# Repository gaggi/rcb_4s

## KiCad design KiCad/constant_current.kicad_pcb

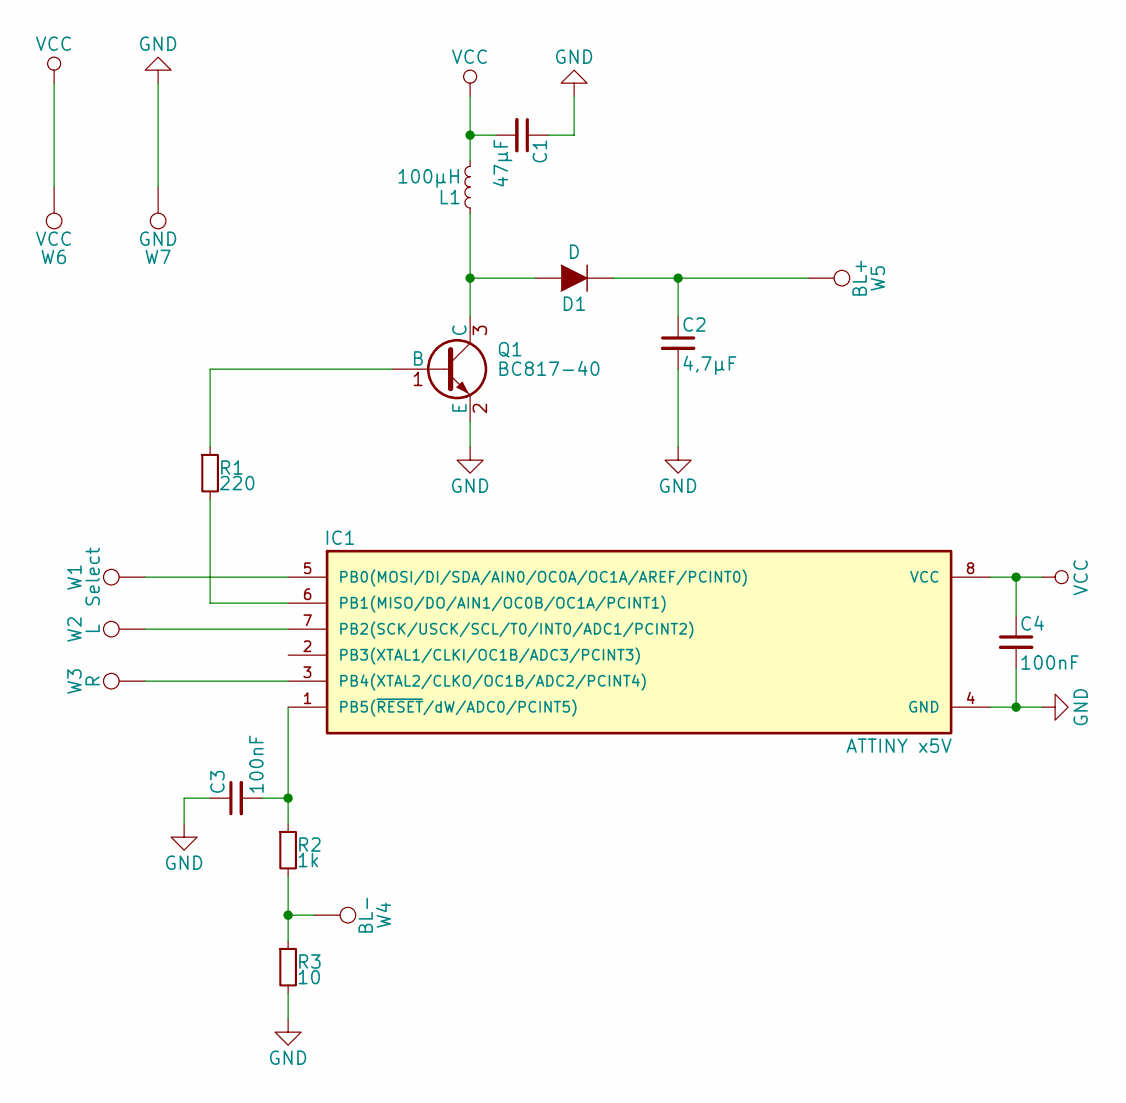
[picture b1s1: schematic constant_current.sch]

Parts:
C1: 47µF; C_1210
C2: 4,7µF; C_1210
C3, C4: 100nF; C_0805
D1: D; D_SOD-323_HandSoldering
IC1: ATTINY x5V; SOIC-8-N
L1: 100µH; 1212fps-inductor
Q1: BC817-40; SOT-23
R1: 220; R_0805
R2: 1k; R_0805
R3: 10; R_0805
W1: Select; 1Pin
W2: L; 1Pin
W3: R; 1Pin
W4: BL-; 1Pin
W5: BL+; 1Pin
W6: VCC; 1Pin
W7: GND; 1Pin

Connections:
GND: C1.1, C2.2, C3.1, C4.2, IC1.4 (GND), Q1.2 (E), R3.2, W7.1; also elsewhere on the board
unnamed: C2.1, D1.1 (K), W5.1
unnamed 2: C3.2, IC1.1 (PB5(~RESET~/dW/ADC0/PCINT5)), R2.1; also elsewhere on the board
unnamed: D1.2 (A), L1.1, Q1.3 (C)
unnamed 4: IC1.3 (PB4(XTAL2/CLKO/OC1B/ADC2/PCINT4)), W3.1; also elsewhere on the board
unnamed 5: IC1.5 (PB0(MOSI/DI/SDA/AIN0/OC0A/OC1A/AREF/PCI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), W1.1; also elsewhere on the board
unnamed 6: IC1.6 (PB1(MISO/DO/AIN1/OC0B/OC1A/PCINT1)), R1.2; also elsewhere on the board
unnamed 7: IC1.7 (PB2(SCK/USCK/SCL/T0/INT0/ADC1/PCINT2)), W2.1; also elsewhere on the board
unnamed: Q1.1 (B), R1.1
unnamed: R2.2, R3.1, W4.1
VCC: C1.2, C4.1, IC1.8 (VCC), L1.2, W6.1; also elsewhere on the board

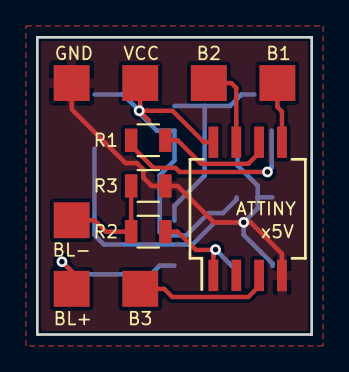
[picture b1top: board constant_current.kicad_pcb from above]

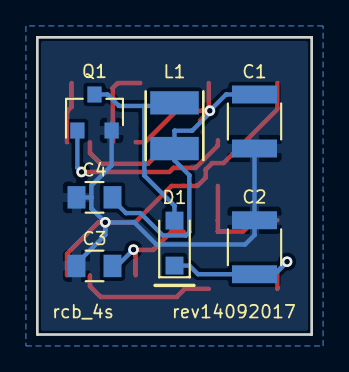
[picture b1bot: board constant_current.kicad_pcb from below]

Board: 2 copper layers, 15.2 x 16.5 mm, 18 parts (7 on the bottom side), 11 nets.

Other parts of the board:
ATTINY: ATTINY; SO-8_5.3x6.2mm_Pitch1.27mm

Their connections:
GND: ATTINY.4; also elsewhere on the board
unnamed 2: ATTINY.1; also elsewhere on the board
unnamed 4: ATTINY.3; also elsewhere on the board
unnamed 5: ATTINY.5; also elsewhere on the board
unnamed 6: ATTINY.6; also elsewhere on the board
unnamed 7: ATTINY.7; also elsewhere on the board
VCC: ATTINY.8; also elsewhere on the board

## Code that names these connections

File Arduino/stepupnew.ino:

/*
  ATtiny lib https://github.com/SpenceKonde/ATTinyCore
  Pin 1 = PB5 = Reset
  Pin 2 = PB3 = A0
  Pin 3 = PB4 = A2
  Pin 4 = GND
  Pin 5 = PB0 = pwm0
  Pin 6 = PB1 = pwm1
  Pon 7 = PB2 = A1
  Pin 8 = VCC
 */
//#include <SoftwareSerial.h>
//#define RX    99                  // no Pin
//#define TX    3                   //  Pin 3

#include <EEPROM.h>
int buttonSelect = 4;             // Pin 3
int buttonUp = 2;                 // Pin 7
int buttonDown = 0;               // Pin 5

int pwmMax = 159;                 // 100kHz

int debounceTime = 100;
int debounceUp = 0;
int debounceDown = 0;
unsigned long buttonTime = 0;

int cTarget = EEPROM.read(1);                // set starting Current to 10.0 mA
int hysteresis = 5;               // plus a hysteresis of 0.3 mA

void setup() {   
//  Serial.begin(9600);
  analogReference(INTERNAL1V1);   // set analog reference to 1.1 Volts
  
  // initialize the digital pin as an output.  
  pinMode(buttonSelect, INPUT_PULLUP);
  pinMode(buttonUp, INPUT_PULLUP);
  pinMode(buttonDown, INPUT_PULLUP);
  pinMode(1, OUTPUT);
   
  PLLCSR = 6;
  TCCR1 = 0xe3;                   // 11100011 PCK/4
  GTCCR = 0;
  
  OCR1C = pwmMax; 
  //OCR1A = 10;
}

void loop() {
  if(digitalRead(buttonUp) == LOW && digitalRead(buttonSelect) == LOW) {
    buttonTime = millis();
    debounceUp = 1;
  }
  if(digitalRead(buttonDown) == LOW && digitalRead(buttonSelect) == LOW) {
    buttonTime = millis();
    debounceDown = 1;
  }

  if(cTarget <= 190 && (millis() - buttonTime > debounceTime) && debounceUp == 1) {
    cTarget += 10;
    debounceUp = 0;
    EEPROM.update(1, cTarget);
  }
  if(cTarget >= 10 && (millis() - buttonTime > debounceTime) && debounceDown == 1) {
    cTarget -= 10;
    debounceDown = 0;
    EEPROM.update(1, cTarget);
  }

  test(cTarget);
}

void test(int target) {
  static int pwm = 0;
  int average = 0;

  for (int x = 0; x < 10; x = x + 1) average += analogRead(A0);
  average = map(average/10, 0, 1023, 0, 1100);

  if(average < target + hysteresis) pwm++;
  else if (average > target + hysteresis) pwm--;

  OCR1A = pwm;
}

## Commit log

2017-09-05 Added KiCad design files
2017-09-05 Changed Footprint of Attiny
2017-09-05 Added Arduino files
2017-09-06 changed inductor footprint
    Changed inductor footprint for easyer handsoldering
2017-09-06 optimized traced
2017-09-06 Minor Layout changes
2017-09-08 changed diode footprint
    Changed the diode footprint to Minimelf
2017-09-14 Code and Layout fixes
